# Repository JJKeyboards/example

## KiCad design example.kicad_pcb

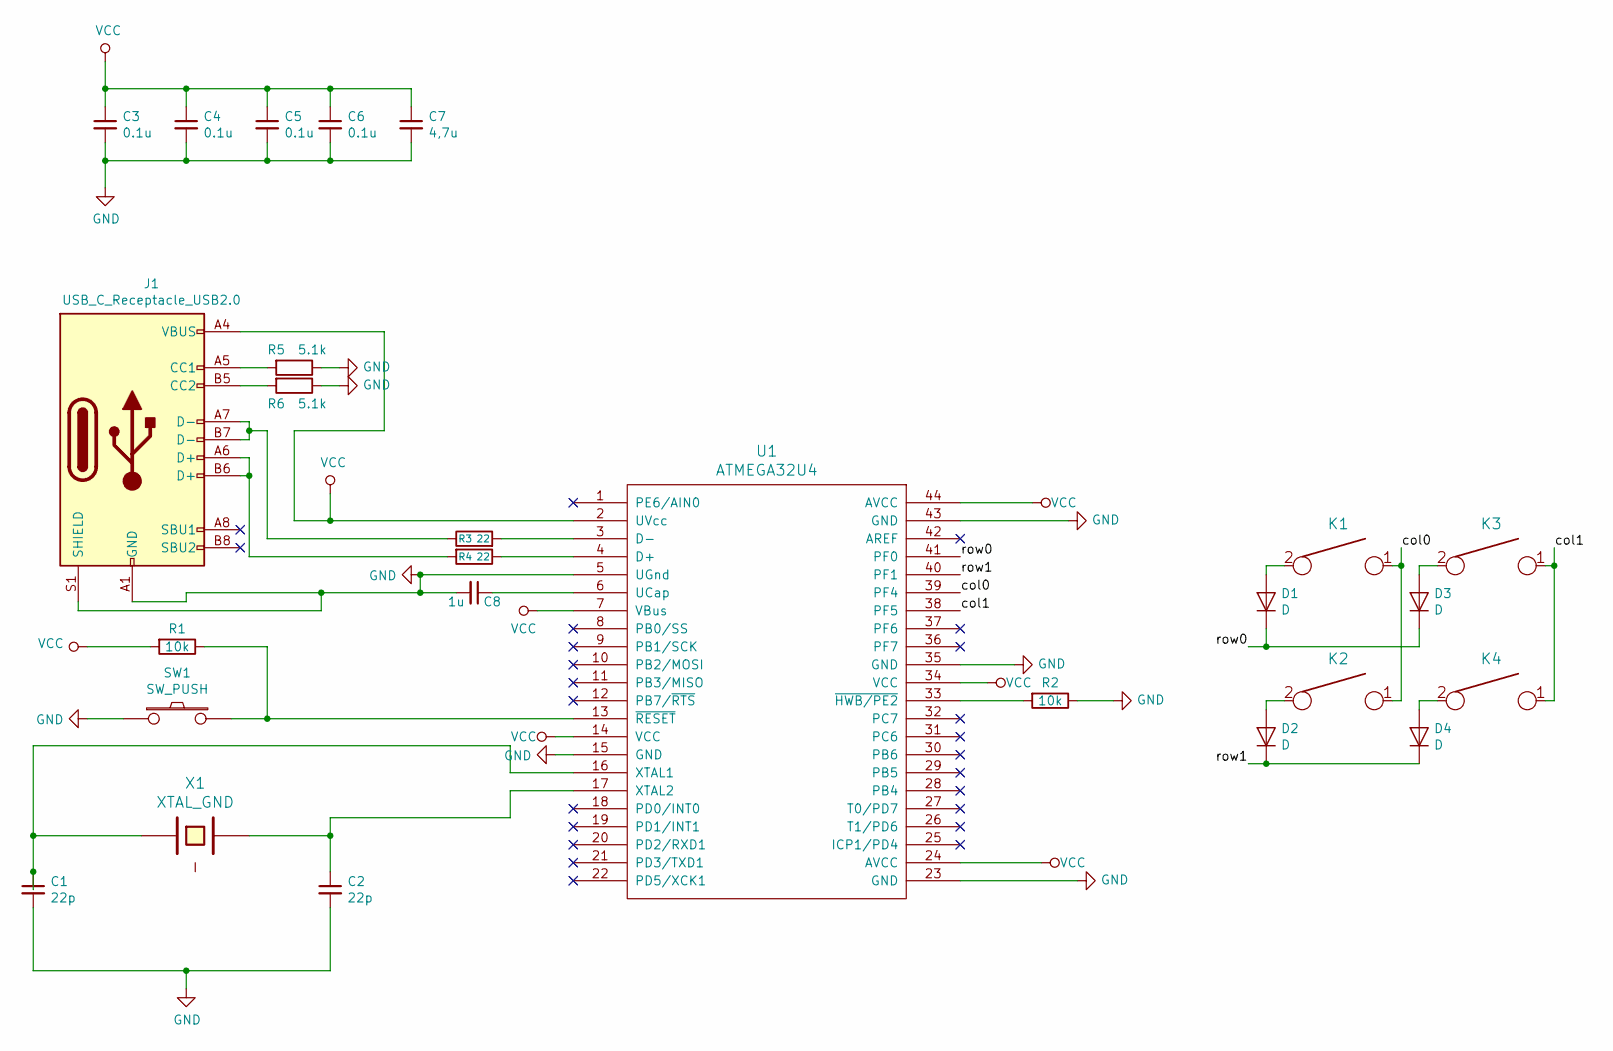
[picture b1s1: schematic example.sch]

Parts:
C1, C2: 22p; C_0805_2012Metric_Pad1.15x1.40mm_HandSolder
C3, C4, C5, C6: 0.1u; C_0805_2012Metric_Pad1.15x1.40mm_HandSolder
C7: 4,7u; C_0603_1608Metric_Pad1.05x0.95mm_HandSolder
C8: 1u; C_0805_2012Metric_Pad1.15x1.40mm_HandSolder
D1, D2, D3, D4: D; D_SOD123_axial
J1: USB_C_Receptacle_USB2.0; USB_C_Receptacle_JAE_DX07S016JA1
K1, K2, K3, K4: KEYSW; Mx_Alps_100
R1, R2: 10k; R_0805_2012Metric_Pad1.15x1.40mm_HandSolder
R3, R4: 22; R_0805_2012Metric_Pad1.15x1.40mm_HandSolder
R5, R6: 5.1k; R_0805_2012Metric_Pad1.15x1.40mm_HandSolder
SW1: SW_PUSH; SW_SPST_TL3342
U1: ATMEGA32U4; TQFP-44_10x10mm_Pitch0.8mm
X1: XTAL_GND; FA-238

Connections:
/col0: K1.1, K2.1, U1.39 (PF4)
/col1: K3.1, K4.1, U1.38 (PF5)
/row0: D1.1 (K), D3.1 (K), U1.41 (PF0)
/row1: D2.1 (K), D4.1 (K), U1.40 (PF1)
GND: C1.2, C2.2, C3.2, C4.2, C5.2, C6.2, C7.2, C8.2, J1.A1 (GND), J1.A12 (GND), J1.B1 (GND), J1.B12 (GND), J1.S1 (SHIELD), R2.1, R5.1, R6.1, SW1.1, U1.5 (UGnd), U1.15 (GND), U1.23 (GND), U1.35 (GND), U1.43 (GND)
unnamed: C1.1, U1.16 (XTAL1), X1.1
unnamed: C2.1, U1.17 (XTAL2), X1.2
unnamed: C8.1, U1.6 (UCap)
unnamed: D1.2 (A), K1.2
unnamed: D2.2 (A), K2.2
unnamed: D3.2 (A), K3.2
unnamed: D4.2 (A), K4.2
unnamed: J1.A5 (CC1), R5.2
unnamed: J1.A6 (D+), J1.B6 (D+), R4.2
unnamed: J1.A7 (D-), J1.B7 (D-), R3.1
unnamed: J1.B5 (CC2), R6.2
unnamed: R1.1, SW1.2, U1.13 (~RESET)
unnamed: R2.2, U1.33 (~HWB/PE2)
unnamed: R3.2, U1.3 (D-)
unnamed: R4.1, U1.4 (D+)
VCC: C3.1, C4.1, C5.1, C6.1, C7.1, J1.A4 (VBUS), J1.A9 (VBUS), J1.B4 (VBUS), J1.B9 (VBUS), R1.2, U1.2 (UVcc), U1.7 (VBus), U1.14 (VCC), U1.24 (AVCC), U1.34 (VCC), U1.44 (AVCC)

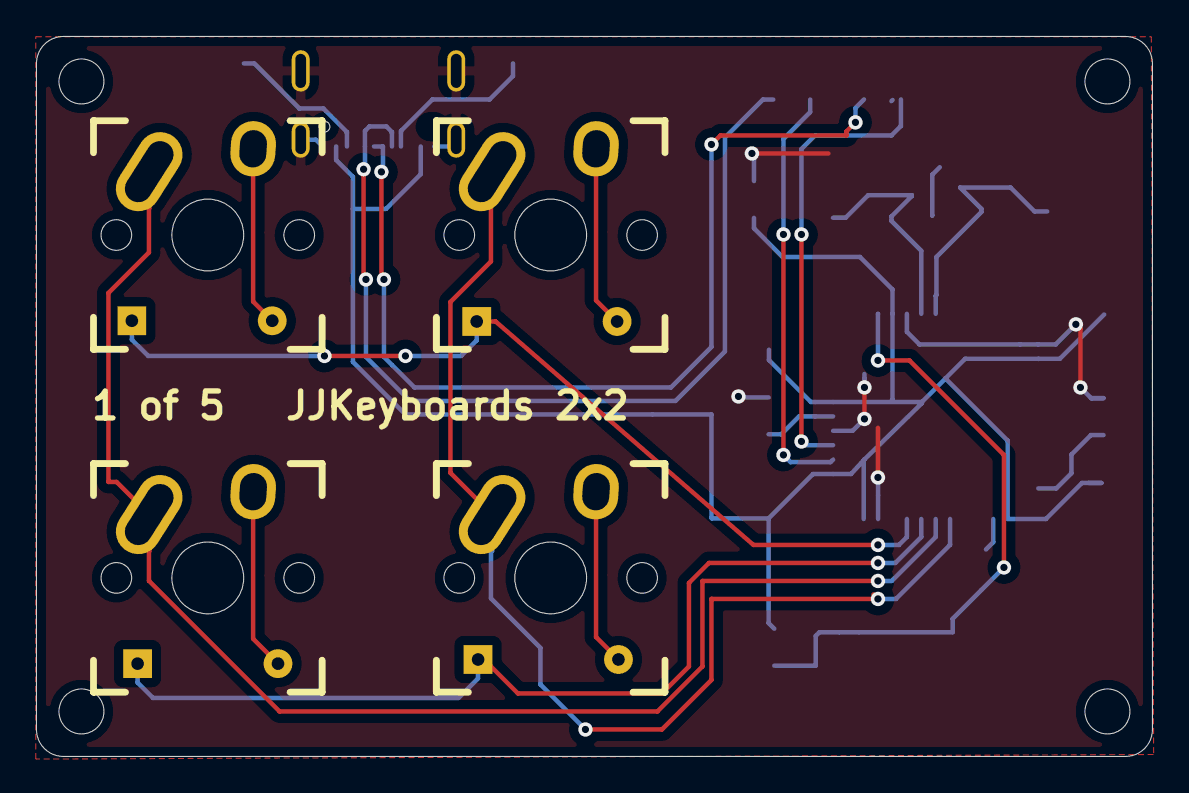
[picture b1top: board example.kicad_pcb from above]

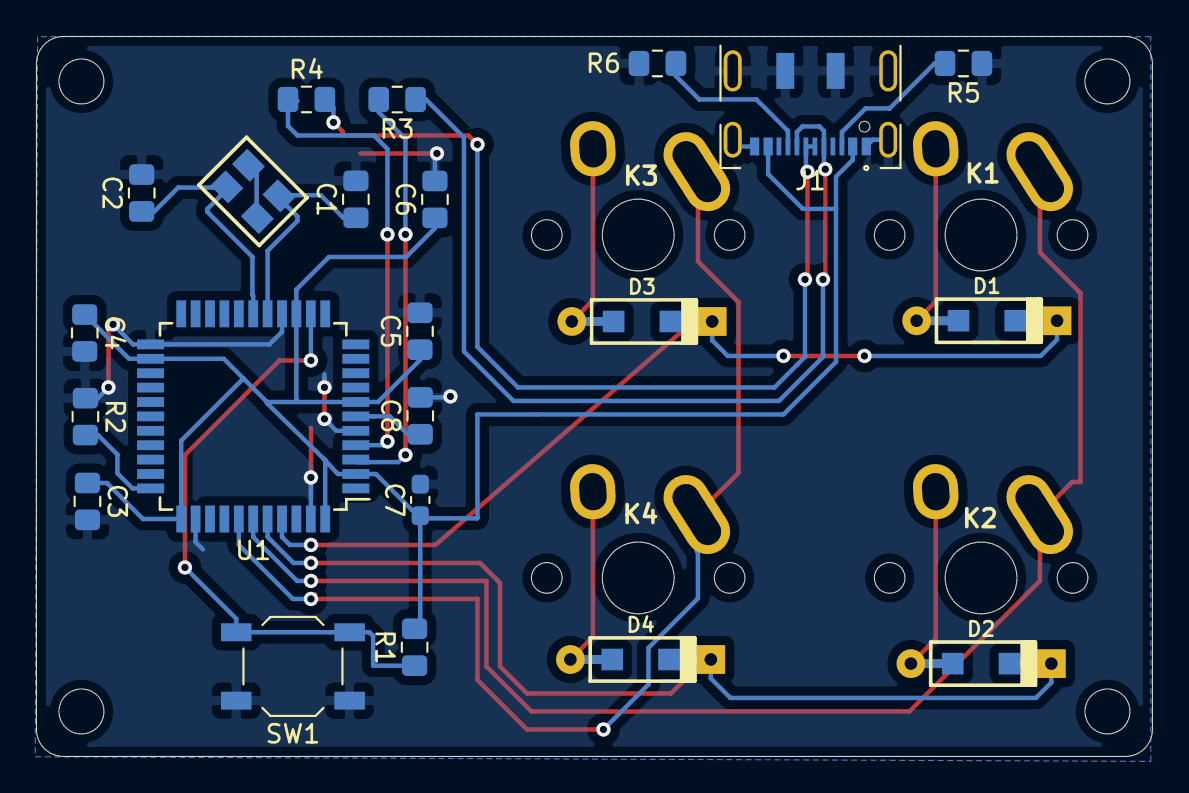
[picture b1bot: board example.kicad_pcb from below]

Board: 2 copper layers, 62.0 x 40.0 mm, 26 parts (22 on the bottom side), 21 nets.
